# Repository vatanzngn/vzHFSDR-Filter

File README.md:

# Six Band 5th-Order Chebyshev Bandpass Filter Board for vzHFSDR HF/VHF

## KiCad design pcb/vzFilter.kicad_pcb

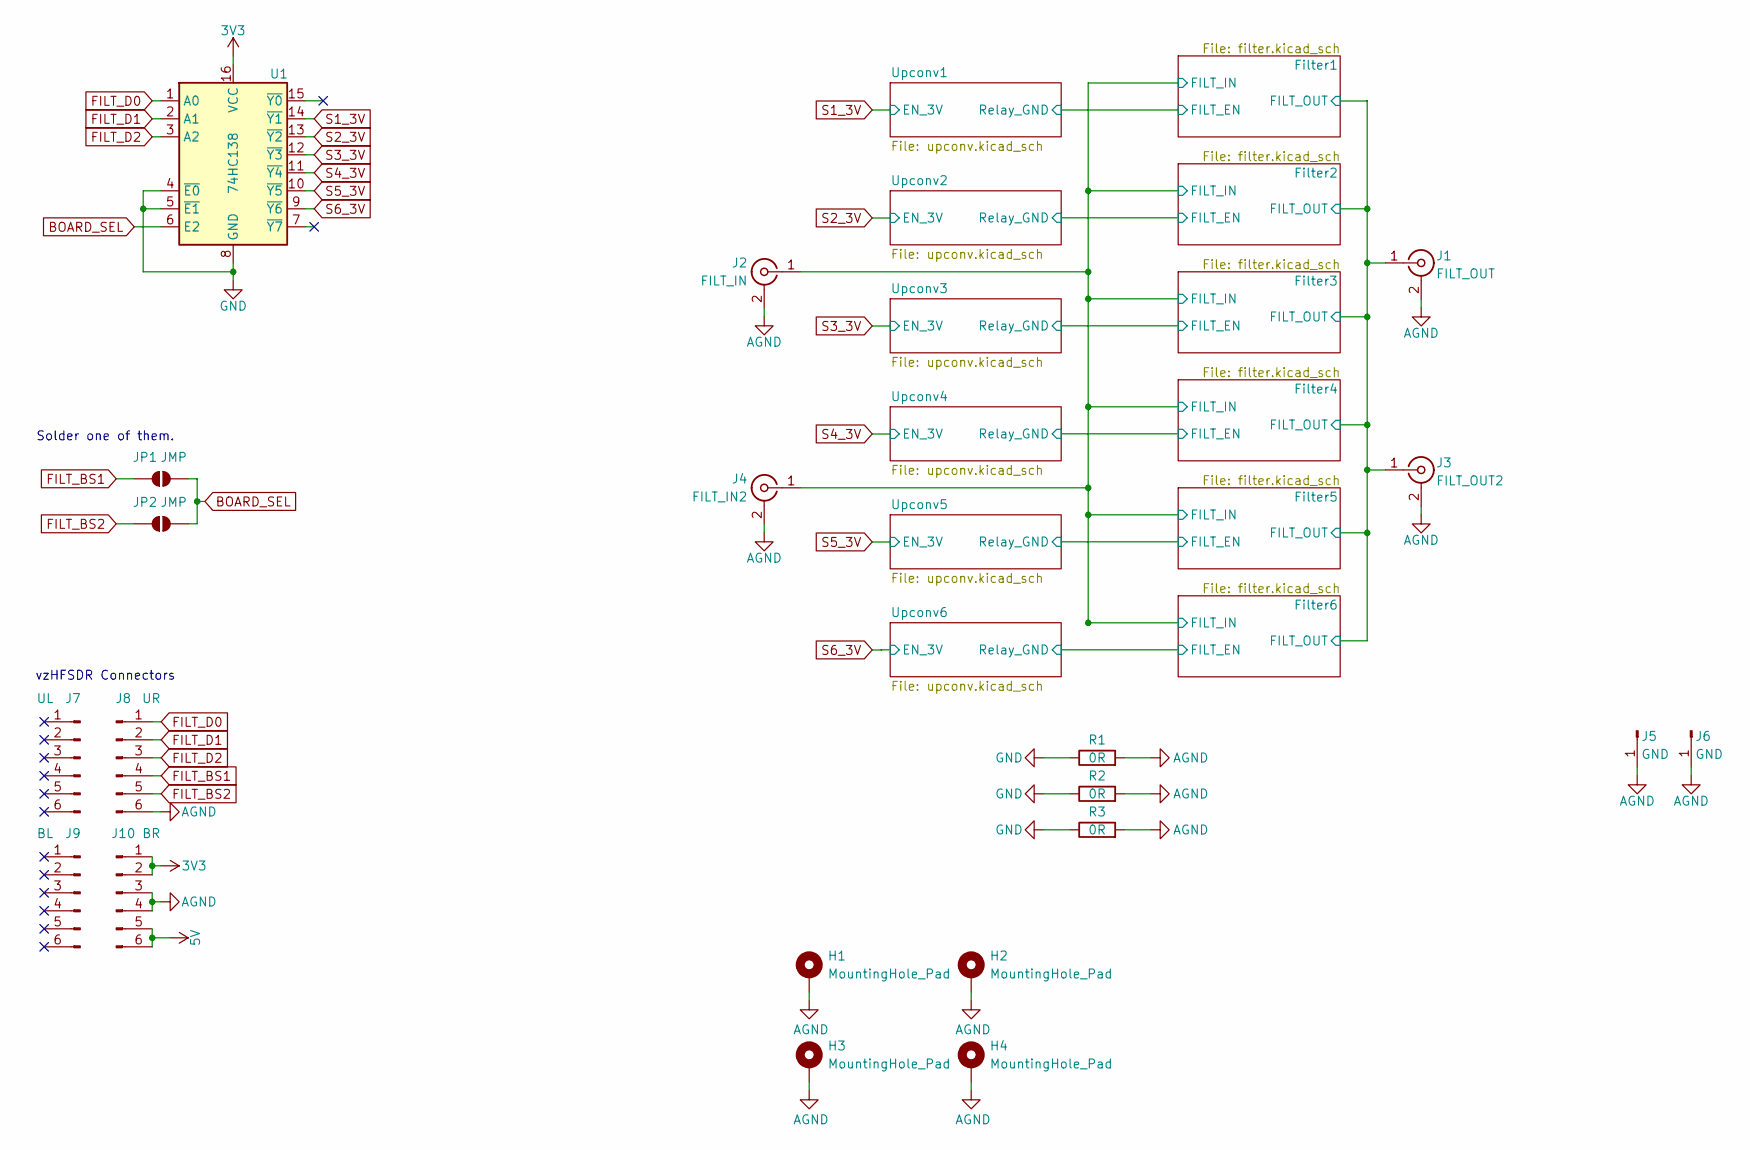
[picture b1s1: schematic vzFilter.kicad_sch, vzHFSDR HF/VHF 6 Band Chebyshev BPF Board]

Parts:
H1, H2, H3, H4: MountingHole_Pad; MountingHole_3.2mm_M3_Pad_Via
J1: FILT_OUT; SMA_BAT_Wireless_BWSMA-KWE-Z001
J2: FILT_IN; SMA_BAT_Wireless_BWSMA-KWE-Z001
J3: FILT_OUT2; SMA_BAT_Wireless_BWSMA-KWE-Z001
J4: FILT_IN2; SMA_BAT_Wireless_BWSMA-KWE-Z001
J5, J6: GND; GroundPad
J7: UL; PinSocket_1x06_P2.54mm_Vertical
J8: UR; PinSocket_1x06_P2.54mm_Vertical
J9: BL; PinSocket_1x06_P2.54mm_Vertical
J10: BR; PinSocket_1x06_P2.54mm_Vertical
JP1, JP2: JMP; SolderJumper-2_P1.3mm_Open_RoundedPad1.0x1.5mm
R1, R2, R3: 0R; R_0805_2012Metric_Pad1.20x1.40mm_HandSolder
U1: 74HC138; SOIC-16_3.9x9.9mm_P1.27mm

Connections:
3V3: J10.1, J10.2, U1.16 (VCC)
5V: J10.5, J10.6; also elsewhere on the board
/Filter1/FILT_IN: J2.1 (In), J4.1 (In); also elsewhere on the board
/Filter1/FILT_OUT: J1.1 (In), J3.1 (In); also elsewhere on the board
AGND: H1.1, H2.1, H3.1, H4.1, J1.2 (Ext), J2.2 (Ext), J3.2 (Ext), J4.2 (Ext), J5.1, J6.1, J8.6, J10.3, J10.4, R1.2, R2.2, R3.2; also elsewhere on the board
BOARD_SEL: JP1.2 (B), JP2.2 (B), U1.6 (E2)
FILT_BS1: J8.4, JP1.1 (A)
FILT_BS2: J8.5, JP2.1 (A)
FILT_D0: J8.1, U1.1 (A0)
FILT_D1: J8.2, U1.2 (A1)
FILT_D2: J8.3, U1.3 (A2)
GND: R1.1, R2.1, R3.1, U1.4 (~E0), U1.5 (~E1), U1.8 (GND); also elsewhere on the board
S1_3V: U1.14 (~Y1); also elsewhere on the board
S2_3V: U1.13 (~Y2); also elsewhere on the board
S3_3V: U1.12 (~Y3); also elsewhere on the board
S4_3V: U1.11 (~Y4); also elsewhere on the board
S5_3V: U1.10 (~Y5); also elsewhere on the board
S6_3V: U1.9 (~Y6); also elsewhere on the board

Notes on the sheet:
Solder one of them.
vzHFSDR Connectors

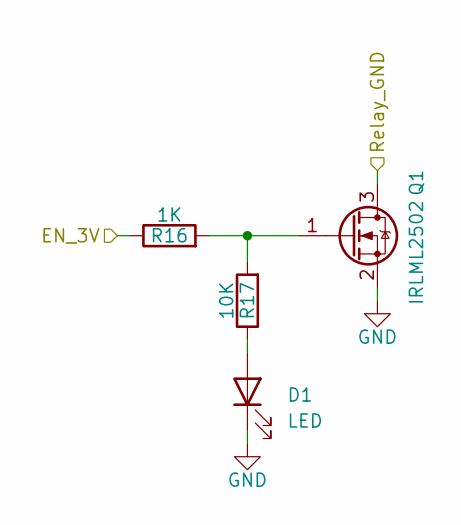
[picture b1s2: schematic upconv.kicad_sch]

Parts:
D1: LED; LED_0805_2012Metric_Pad1.15x1.40mm_HandSolder
Q1: IRLML2502; SOT-23
R16: 1K; R_0805_2012Metric_Pad1.20x1.40mm_HandSolder
R17: 10K; R_0805_2012Metric_Pad1.20x1.40mm_HandSolder

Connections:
/Filter1/FILT_EN: Q1.3 (D); also elsewhere on the board
GND: D1.1 (K), Q1.2 (S); also elsewhere on the board
unnamed: D1.2 (A), R17.1
unnamed: Q1.1 (G), R16.2, R17.2
S1_3V: R16.1; also elsewhere on the board

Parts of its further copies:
D2, D3, D4, D5, D6: LED; LED_0805_2012Metric_Pad1.15x1.40mm_HandSolder
Q2, Q3, Q4, Q5, Q6: IRLML2502; SOT-23
R18, R20, R22, R24, R26: 1K; R_0805_2012Metric_Pad1.20x1.40mm_HandSolder
R19, R21, R23, R25, R27: 10K; R_0805_2012Metric_Pad1.20x1.40mm_HandSolder

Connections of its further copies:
/Filter2/FILT_EN: Q2.3 (D); also elsewhere on the board
/Filter3/FILT_EN: Q3.3 (D); also elsewhere on the board
/Filter4/FILT_EN: Q4.3 (D); also elsewhere on the board
/Filter5/FILT_EN: Q5.3 (D); also elsewhere on the board
/Filter6/FILT_EN: Q6.3 (D); also elsewhere on the board
GND: D2.1 (K), D3.1 (K), D4.1 (K), D5.1 (K), D6.1 (K), Q2.2 (S), Q3.2 (S), Q4.2 (S), Q5.2 (S), Q6.2 (S); also elsewhere on the board
unnamed: D2.2 (A), R19.1
unnamed: D3.2 (A), R21.1
unnamed: D4.2 (A), R23.1
unnamed: D5.2 (A), R25.1
unnamed: D6.2 (A), R27.1
unnamed: Q2.1 (G), R18.2, R19.2
unnamed: Q3.1 (G), R20.2, R21.2
unnamed: Q4.1 (G), R22.2, R23.2
unnamed: Q5.1 (G), R24.2, R25.2
unnamed: Q6.1 (G), R26.2, R27.2
S2_3V: R18.1; also elsewhere on the board
S3_3V: R20.1; also elsewhere on the board
S4_3V: R22.1; also elsewhere on the board
S5_3V: R24.1; also elsewhere on the board
S6_3V: R26.1; also elsewhere on the board

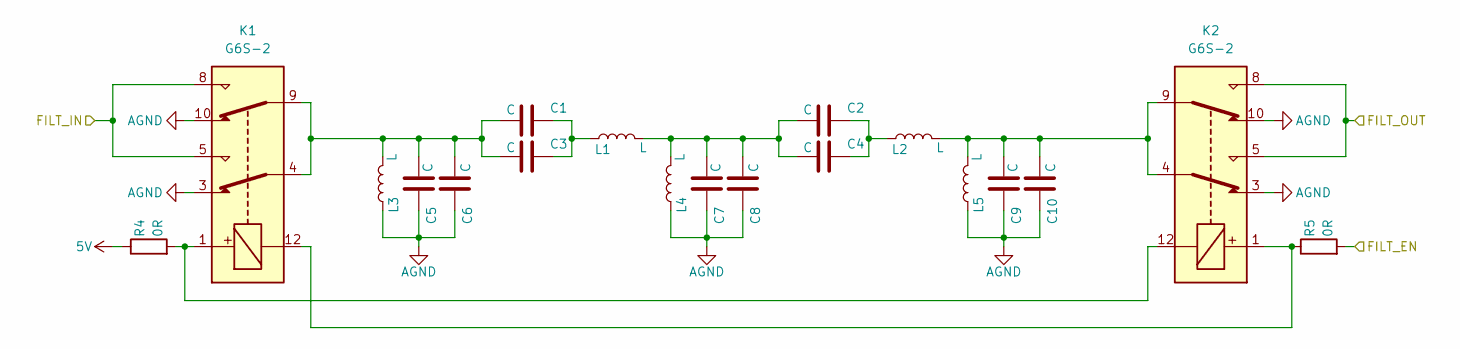
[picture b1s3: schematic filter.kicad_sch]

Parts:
C1, C2, C3, C4, C5, C6, C7, C8, C9, C10: C; C_0805_2012Metric_Pad1.18x1.45mm_HandSolder
K1, K2: G6S-2; Relay_DPDT_Omron_G6S-2
L1, L2, L3, L4, L5: L; T68-2 Toroid
R4, R5: 0R; R_1206_3216Metric

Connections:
5V: R4.1; also elsewhere on the board
/Filter1/FILT_EN: R5.2; also elsewhere on the board
/Filter1/FILT_IN: K1.5, K1.8; also elsewhere on the board
/Filter1/FILT_OUT: K2.5, K2.8; also elsewhere on the board
AGND: C5.2, C6.2, C7.2, C8.2, C9.2, C10.2, K1.3, K1.10, K2.3, K2.10, L3.1, L4.1, L5.1; also elsewhere on the board
unnamed: C1.1, C3.1, C5.1, C6.1, K1.4, K1.9, L3.2
unnamed: C1.2, C3.2, L1.1
unnamed: C2.1, C4.1, C7.1, C8.1, L1.2, L4.2
unnamed: C2.2, C4.2, L2.1
unnamed: C9.1, C10.1, K2.4, K2.9, L2.2, L5.2
unnamed: K1.1, K2.12, R4.2
unnamed: K1.12, K2.1, R5.1

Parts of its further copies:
C11, C12, C13, C14, C15, C16, C17, C18, C19, C20, C21, C22, C23, C24, C25, C26, C27, C28, C29, C30, C31, C32, C33, C34, C35, C36, C37, C38, C39, C40, C41, C42, C43, C44, C45, C46, C47, C48, C49, C50, C51, C52, C53, C54, C55, C56, C57, C58, C59, C60: C; C_0805_2012Metric_Pad1.18x1.45mm_HandSolder
K3, K4, K5, K6, K7, K8, K9, K10, K11, K12: G6S-2; Relay_DPDT_Omron_G6S-2
L6, L7, L8, L9, L10, L11, L12, L13, L14, L15, L16, L17, L18, L19, L20, L21, L22, L23, L24, L25, L26, L27, L28, L29, L30: L; T68-2 Toroid
R6, R7, R8, R9, R10, R11, R12, R13, R14, R15: 0R; R_1206_3216Metric

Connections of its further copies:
5V: R6.1, R8.1, R10.1, R12.1, R14.1; also elsewhere on the board
/Filter1/FILT_IN: K3.5, K3.8, K5.5, K5.8, K7.5, K7.8, K9.5, K9.8, K11.5, K11.8; also elsewhere on the board
/Filter1/FILT_OUT: K4.5, K4.8, K6.5, K6.8, K8.5, K8.8, K10.5, K10.8, K12.5, K12.8; also elsewhere on the board
/Filter2/FILT_EN: R7.2; also elsewhere on the board
/Filter3/FILT_EN: R9.2; also elsewhere on the board
/Filter4/FILT_EN: R11.2; also elsewhere on the board
/Filter5/FILT_EN: R13.2; also elsewhere on the board
/Filter6/FILT_EN: R15.2; also elsewhere on the board
AGND: C15.2, C16.2, C17.2, C18.2, C19.2, C20.2, C25.2, C26.2, C27.2, C28.2, C29.2, C30.2, C35.2, C36.2, C37.2, C38.2, C39.2, C40.2, C45.2, C46.2, C47.2, C48.2, C49.2, C50.2, C55.2, C56.2, C57.2, C58.2, C59.2, C60.2, K3.3, K3.10, K4.3, K4.10, K5.3, K5.10, K6.3, K6.10, K7.3, K7.10, K8.3, K8.10, K9.3, K9.10, K10.3, K10.10, K11.3, K11.10, K12.3, K12.10, L8.1, L9.1, L10.1, L13.1, L14.1, L15.1, L18.1, L19.1, L20.1, L23.1, L24.1, L25.1, L28.1, L29.1, L30.1; also elsewhere on the board
unnamed: C11.1, C13.1, C15.1, C16.1, K3.4, K3.9, L8.2
unnamed: C11.2, C13.2, L6.1
unnamed: C12.1, C14.1, C17.1, C18.1, L6.2, L9.2
unnamed: C12.2, C14.2, L7.1
unnamed: C19.1, C20.1, K4.4, K4.9, L7.2, L10.2
unnamed: C21.1, C23.1, C25.1, C26.1, K5.4, K5.9, L13.2
unnamed: C21.2, C23.2, L11.1
unnamed: C22.1, C24.1, C27.1, C28.1, L11.2, L14.2
unnamed: C22.2, C24.2, L12.1
unnamed: C29.1, C30.1, K6.4, K6.9, L12.2, L15.2
unnamed: C31.1, C33.1, C35.1, C36.1, K7.4, K7.9, L18.2
unnamed: C31.2, C33.2, L16.1
unnamed: C32.1, C34.1, C37.1, C38.1, L16.2, L19.2
unnamed: C32.2, C34.2, L17.1
unnamed: C39.1, C40.1, K8.4, K8.9, L17.2, L20.2
unnamed: C41.1, C43.1, C45.1, C46.1, K9.4, K9.9, L23.2
unnamed: C41.2, C43.2, L21.1
unnamed: C42.1, C44.1, C47.1, C48.1, L21.2, L24.2
unnamed: C42.2, C44.2, L22.1
unnamed: C49.1, C50.1, K10.4, K10.9, L22.2, L25.2
unnamed: C51.1, C53.1, C55.1, C56.1, K11.4, K11.9, L28.2
unnamed: C51.2, C53.2, L26.1
unnamed: C52.1, C54.1, C57.1, C58.1, L26.2, L29.2
unnamed: C52.2, C54.2, L27.1
unnamed: C59.1, C60.1, K12.4, K12.9, L27.2, L30.2
unnamed: K3.1, K4.12, R6.2
unnamed: K3.12, K4.1, R7.1
unnamed: K5.1, K6.12, R8.2
unnamed: K5.12, K6.1, R9.1
unnamed: K7.1, K8.12, R10.2
unnamed: K7.12, K8.1, R11.1
unnamed: K9.12, K10.1, R13.1
unnamed: K9.1, K10.12, R12.2
unnamed: K11.1, K12.12, R14.2
unnamed: K11.12, K12.1, R15.1

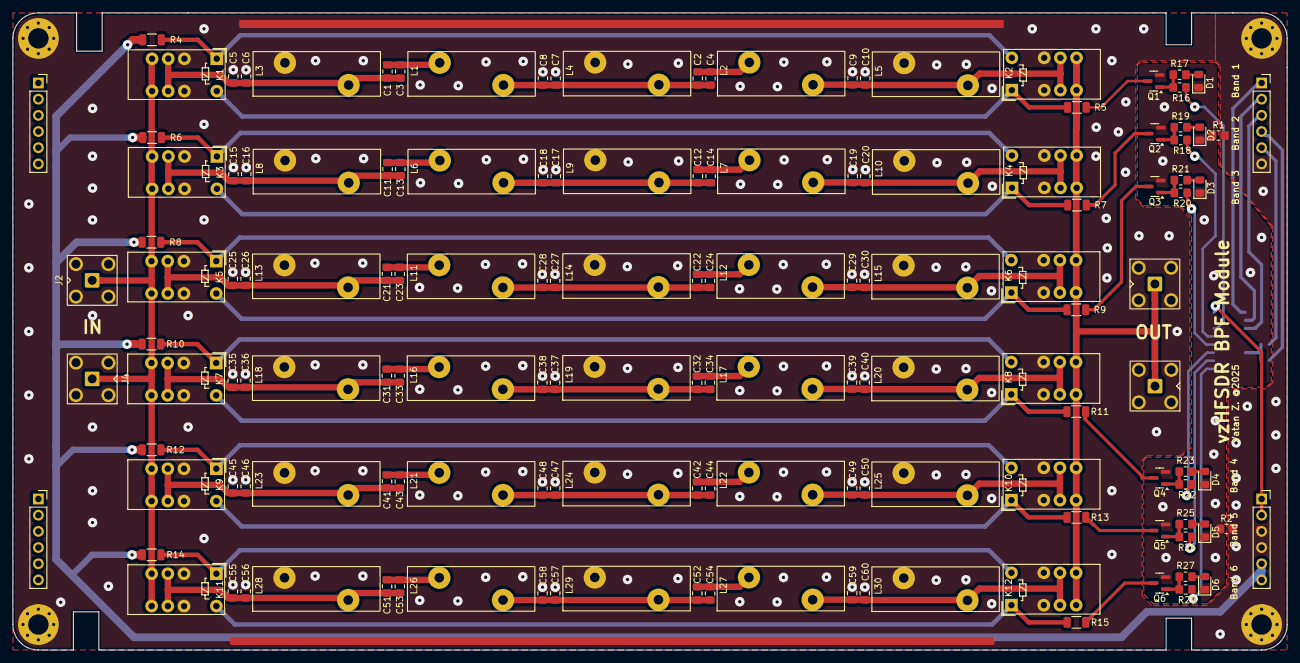
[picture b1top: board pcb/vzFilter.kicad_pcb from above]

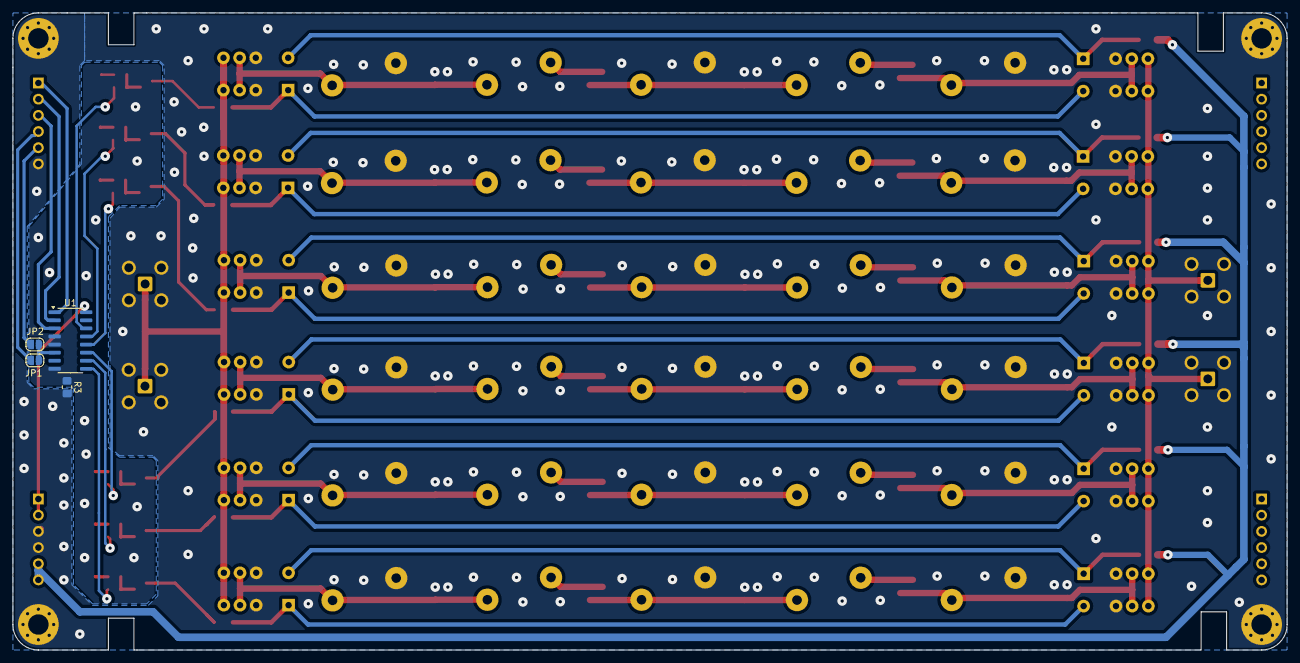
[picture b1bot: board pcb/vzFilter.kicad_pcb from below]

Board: 2 copper layers, 200.0 x 100.0 mm, 158 parts (4 on the bottom side), 78 nets.

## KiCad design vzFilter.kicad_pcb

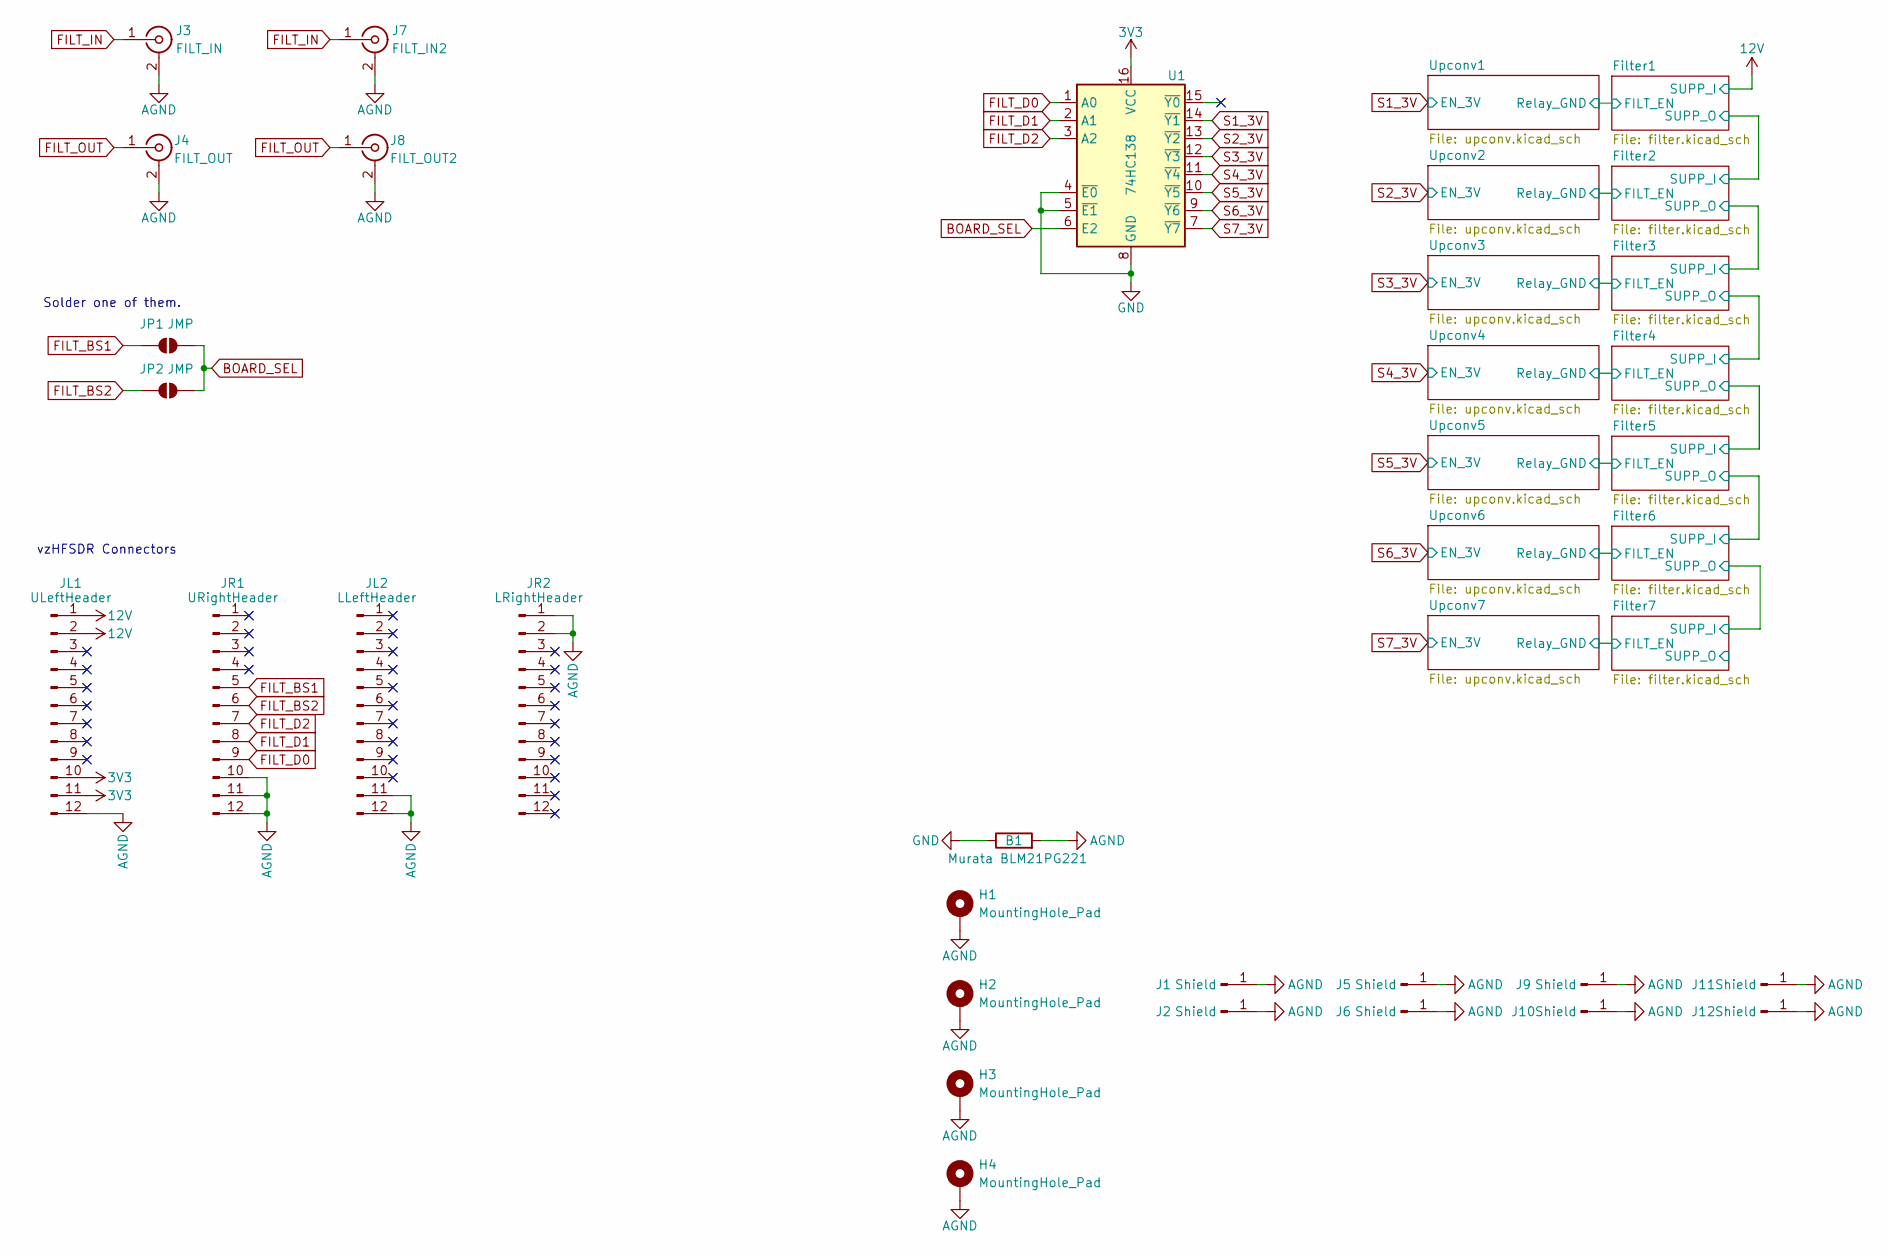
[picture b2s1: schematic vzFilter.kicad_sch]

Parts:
B1: Murata BLM21PG221; R_0805_2012Metric
H1, H2, H3, H4: MountingHole_Pad; MountingHole_3.2mm_M3_ISO14580_Pad_TopBottom
J1, J2, J5, J6, J9, J10, J11, J12: Shield; Untitled_2
J3: FILT_IN; U.FL_Molex_MCRF_73412-0110_Vertical
J4: FILT_OUT; U.FL_Molex_MCRF_73412-0110_Vertical
J7: FILT_IN2; U.FL_Molex_MCRF_73412-0110_Vertical
J8: FILT_OUT2; U.FL_Molex_MCRF_73412-0110_Vertical
JL1: ULeftHeader; PinSocket_1x12_P2.54mm_Vertical
JL2: LLeftHeader; PinSocket_1x12_P2.54mm_Vertical
JP1, JP2: JMP; SolderJumper-2_P1.3mm_Open_RoundedPad1.0x1.5mm
JR1: URightHeader; PinSocket_1x12_P2.54mm_Vertical
JR2: LRightHeader; PinSocket_1x12_P2.54mm_Vertical
U1: 74HC138; SOIC-16_3.9x9.9mm_P1.27mm

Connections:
3V3: JL1.10, JL1.11, U1.16 (VCC)
12V: JL1.1, JL1.2; also elsewhere on the board
AGND: B1.2, H1.1, H2.1, H3.1, H4.1, J1.1, J2.1, J3.2 (Ext), J4.2 (Ext), J5.1, J6.1, J7.2 (Ext), J8.2 (Ext), J9.1, J10.1, J11.1, J12.1, JL1.12, JL2.11, JL2.12, JR1.10, JR1.11, JR1.12, JR2.1, JR2.2; also elsewhere on the board
BOARD_SEL: JP1.2 (B), JP2.2 (B), U1.6 (E2)
FILT_BS1: JP1.1 (A), JR1.5
FILT_BS2: JP2.1 (A), JR1.6
FILT_D0: JR1.9, U1.1 (A0)
FILT_D1: JR1.8, U1.2 (A1)
FILT_D2: JR1.7, U1.3 (A2)
FILT_IN: J3.1 (In), J7.1 (In); also elsewhere on the board
FILT_OUT: J4.1 (In), J8.1 (In); also elsewhere on the board
GND: B1.1, U1.4 (~E0), U1.5 (~E1), U1.8 (GND); also elsewhere on the board
S1_3V: U1.14 (~Y1); also elsewhere on the board
S2_3V: U1.13 (~Y2); also elsewhere on the board
S3_3V: U1.12 (~Y3); also elsewhere on the board
S4_3V: U1.11 (~Y4); also elsewhere on the board
S5_3V: U1.10 (~Y5); also elsewhere on the board
S6_3V: U1.9 (~Y6); also elsewhere on the board
S7_3V: U1.7 (~Y7); also elsewhere on the board

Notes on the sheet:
Solder one of them.
vzHFSDR Connectors

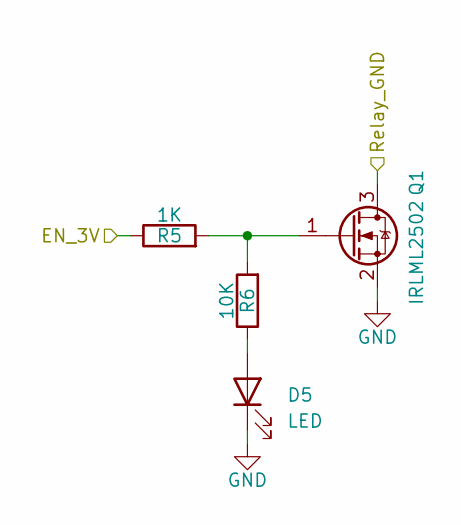
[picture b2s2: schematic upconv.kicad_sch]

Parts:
D5: LED; LED_0805_2012Metric_Pad1.15x1.40mm_HandSolder
Q1: IRLML2502; SOT-23
R5: 1K; R_0805_2012Metric_Pad1.20x1.40mm_HandSolder
R6: 10K; R_0805_2012Metric_Pad1.20x1.40mm_HandSolder

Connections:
/Filter2/FILT_EN: Q1.3 (D); also elsewhere on the board
GND: D5.1 (K), Q1.2 (S); also elsewhere on the board
unnamed: D5.2 (A), R6.1
unnamed: Q1.1 (G), R5.2, R6.2
S2_3V: R5.1; also elsewhere on the board

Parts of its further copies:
D8, D11, D12, D15, D18, D21: LED; LED_0805_2012Metric_Pad1.15x1.40mm_HandSolder
Q2, Q3, Q4, Q5, Q6, Q7: IRLML2502; SOT-23
R9, R13, R15, R19, R23, R27: 1K; R_0805_2012Metric_Pad1.20x1.40mm_HandSolder
R10, R14, R16, R20, R24, R28: 10K; R_0805_2012Metric_Pad1.20x1.40mm_HandSolder

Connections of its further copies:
/Filter1/FILT_EN: Q3.3 (D); also elsewhere on the board
/Filter3/FILT_EN: Q2.3 (D); also elsewhere on the board
/Filter4/FILT_EN: Q4.3 (D); also elsewhere on the board
/Filter5/FILT_EN: Q5.3 (D); also elsewhere on the board
/Filter6/FILT_EN: Q6.3 (D); also elsewhere on the board
/Filter7/FILT_EN: Q7.3 (D); also elsewhere on the board
GND: D8.1 (K), D11.1 (K), D12.1 (K), D15.1 (K), D18.1 (K), D21.1 (K), Q2.2 (S), Q3.2 (S), Q4.2 (S), Q5.2 (S), Q6.2 (S), Q7.2 (S); also elsewhere on the board
unnamed: D8.2 (A), R10.1
unnamed: D11.2 (A), R14.1
unnamed: D12.2 (A), R16.1
unnamed: D15.2 (A), R20.1
unnamed: D18.2 (A), R24.1
unnamed: D21.2 (A), R28.1
unnamed: Q2.1 (G), R9.2, R10.2
unnamed: Q3.1 (G), R13.2, R14.2
unnamed: Q4.1 (G), R15.2, R16.2
unnamed: Q5.1 (G), R19.2, R20.2
unnamed: Q6.1 (G), R23.2, R24.2
unnamed: Q7.1 (G), R27.2, R28.2
S1_3V: R13.1; also elsewhere on the board
S3_3V: R9.1; also elsewhere on the board
S4_3V: R15.1; also elsewhere on the board
S5_3V: R19.1; also elsewhere on the board
S6_3V: R23.1; also elsewhere on the board
S7_3V: R27.1; also elsewhere on the board

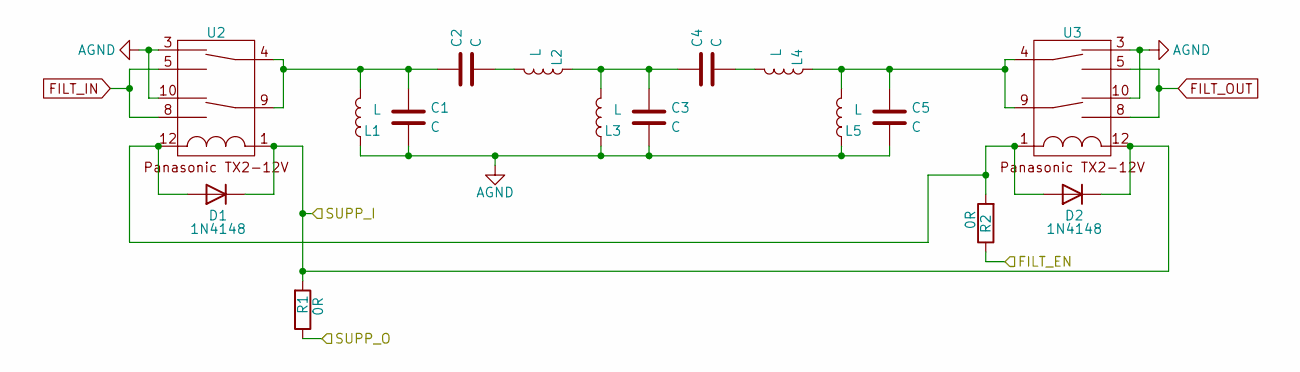
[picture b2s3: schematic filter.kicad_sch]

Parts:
C1, C2, C3, C4, C5: C; C_0805_2012Metric_Pad1.18x1.45mm_HandSolder
D1, D2: 1N4148; D_DO-35_SOD27_P7.62mm_Horizontal
L1, L2, L3, L4, L5: L; vz_torroite_t68
R1, R2: 0R; R_1210_3225Metric_Pad1.30x2.65mm_HandSolder
U2, U3: TX2_Panasonic

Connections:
12V: D1.1 (K), D2.1 (K), R1.2, U2.1, U3.12; also elsewhere on the board
/Filter1/FILT_EN: R2.1; also elsewhere on the board
/Filter1/SUPP_O: R1.1; also elsewhere on the board
AGND: C1.2, C3.2, C5.2, L1.1, L3.1, L5.1, U2.3, U2.10, U3.3, U3.10; also elsewhere on the board
FILT_IN: U2.5, U2.8; also elsewhere on the board
FILT_OUT: U3.5, U3.8; also elsewhere on the board
unnamed: C1.1, C2.1, L1.2, U2.4, U2.9
unnamed: C2.2, L2.2
unnamed: C3.1, C4.1, L2.1, L3.2
unnamed: C4.2, L4.2
unnamed: C5.1, L4.1, L5.2, U3.4, U3.9
unnamed: D1.2 (A), D2.2 (A), R2.2, U2.12, U3.1

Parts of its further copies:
C6, C7, C8, C9, C10, C11, C12, C13, C14, C15, C16, C17, C18, C19, C20, C21, C22, C23, C24, C25, C26, C27, C28, C29, C30, C31, C32, C33, C34, C35: C; C_0805_2012Metric_Pad1.18x1.45mm_HandSolder
D3, D4, D6, D7, D9, D10, D13, D14, D16, D17, D19, D20: 1N4148; D_DO-35_SOD27_P7.62mm_Horizontal
L6, L7, L8, L9, L10, L11, L12, L13, L14, L15, L16, L17, L18, L19, L20, L21, L22, L23, L24, L25, L26, L27, L28, L29, L30, L31, L32, L33, L34, L35: L; vz_torroite_t68
R3, R4, R7, R8, R11, R12, R17, R18, R21, R22, R25, R26: 0R; R_1210_3225Metric_Pad1.30x2.65mm_HandSolder
U4, U5, U6, U7, U8, U9, U10, U11, U12, U13, U14, U15: TX2_Panasonic

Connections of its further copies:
/Filter1/SUPP_O: D3.1 (K), D4.1 (K), R3.2, U4.1, U5.12; also elsewhere on the board
/Filter2/FILT_EN: R4.1; also elsewhere on the board
/Filter2/SUPP_O: D6.1 (K), D7.1 (K), R3.1, R7.2, U6.1, U7.12
/Filter3/FILT_EN: R8.1; also elsewhere on the board
/Filter3/SUPP_O: D9.1 (K), D10.1 (K), R7.1, R11.2, U8.1, U9.12
/Filter4/FILT_EN: R12.1; also elsewhere on the board
/Filter4/SUPP_O: D13.1 (K), D14.1 (K), R11.1, R17.2, U10.1, U11.12
/Filter5/FILT_EN: R18.1; also elsewhere on the board
/Filter5/SUPP_O: D16.1 (K), D17.1 (K), R17.1, R21.2, U12.1, U13.12
/Filter6/FILT_EN: R22.1; also elsewhere on the board
/Filter6/SUPP_O: D19.1 (K), D20.1 (K), R21.1, R25.2, U14.1, U15.12
/Filter7/FILT_EN: R26.1; also elsewhere on the board
/Filter7/SUPP_O: R25.1
AGND: C6.2, C8.2, C10.2, C11.2, C13.2, C15.2, C16.2, C18.2, C20.2, C21.2, C23.2, C25.2, C26.2, C28.2, C30.2, C31.2, C33.2, C35.2, L6.1, L8.1, L10.1, L11.1, L13.1, L15.1, L16.1, L18.1, L20.1, L21.1, L23.1, L25.1, L26.1, L28.1, L30.1, L31.1, L33.1, L35.1, U4.3, U4.10, U5.3, U5.10, U6.3, U6.10, U7.3, U7.10, U8.3, U8.10, U9.3, U9.10, U10.3, U10.10, U11.3, U11.10, U12.3, U12.10, U13.3, U13.10, U14.3, U14.10, U15.3, U15.10; also elsewhere on the board
FILT_IN: U4.5, U4.8, U6.5, U6.8, U8.5, U8.8, U10.5, U10.8, U12.5, U12.8, U14.5, U14.8; also elsewhere on the board
FILT_OUT: U5.5, U5.8, U7.5, U7.8, U9.5, U9.8, U11.5, U11.8, U13.5, U13.8, U15.5, U15.8; also elsewhere on the board
unnamed: C6.1, C7.1, L6.2, U4.4, U4.9
unnamed: C7.2, L7.2
unnamed: C8.1, C9.1, L7.1, L8.2
unnamed: C9.2, L9.2
unnamed: C10.1, L9.1, L10.2, U5.4, U5.9
unnamed: C11.1, C12.1, L11.2, U6.4, U6.9
unnamed: C12.2, L12.2
unnamed: C13.1, C14.1, L12.1, L13.2
unnamed: C14.2, L14.2
unnamed: C15.1, L14.1, L15.2, U7.4, U7.9
unnamed: C16.1, C17.1, L16.2, U8.4, U8.9
unnamed: C17.2, L17.2
unnamed: C18.1, C19.1, L17.1, L18.2
unnamed: C19.2, L19.2
unnamed: C20.1, L19.1, L20.2, U9.4, U9.9
unnamed: C21.1, C22.1, L21.2, U10.4, U10.9
unnamed: C22.2, L22.2
unnamed: C23.1, C24.1, L22.1, L23.2
unnamed: C24.2, L24.2
unnamed: C25.1, L24.1, L25.2, U11.4, U11.9
unnamed: C26.1, C27.1, L26.2, U12.4, U12.9
unnamed: C27.2, L27.2
unnamed: C28.1, C29.1, L27.1, L28.2
unnamed: C29.2, L29.2
unnamed: C30.1, L29.1, L30.2, U13.4, U13.9
unnamed: C31.1, C32.1, L31.2, U14.4, U14.9
unnamed: C32.2, L32.2
unnamed: C33.1, C34.1, L32.1, L33.2
unnamed: C34.2, L34.2
unnamed: C35.1, L34.1, L35.2, U15.4, U15.9
unnamed: D3.2 (A), D4.2 (A), R4.2, U4.12, U5.1
unnamed: D6.2 (A), D7.2 (A), R8.2, U6.12, U7.1
unnamed: D9.2 (A), D10.2 (A), R12.2, U8.12, U9.1
unnamed: D13.2 (A), D14.2 (A), R18.2, U10.12, U11.1
unnamed: D16.2 (A), D17.2 (A), R22.2, U12.12, U13.1
unnamed: D19.2 (A), D20.2 (A), R26.2, U14.12, U15.1

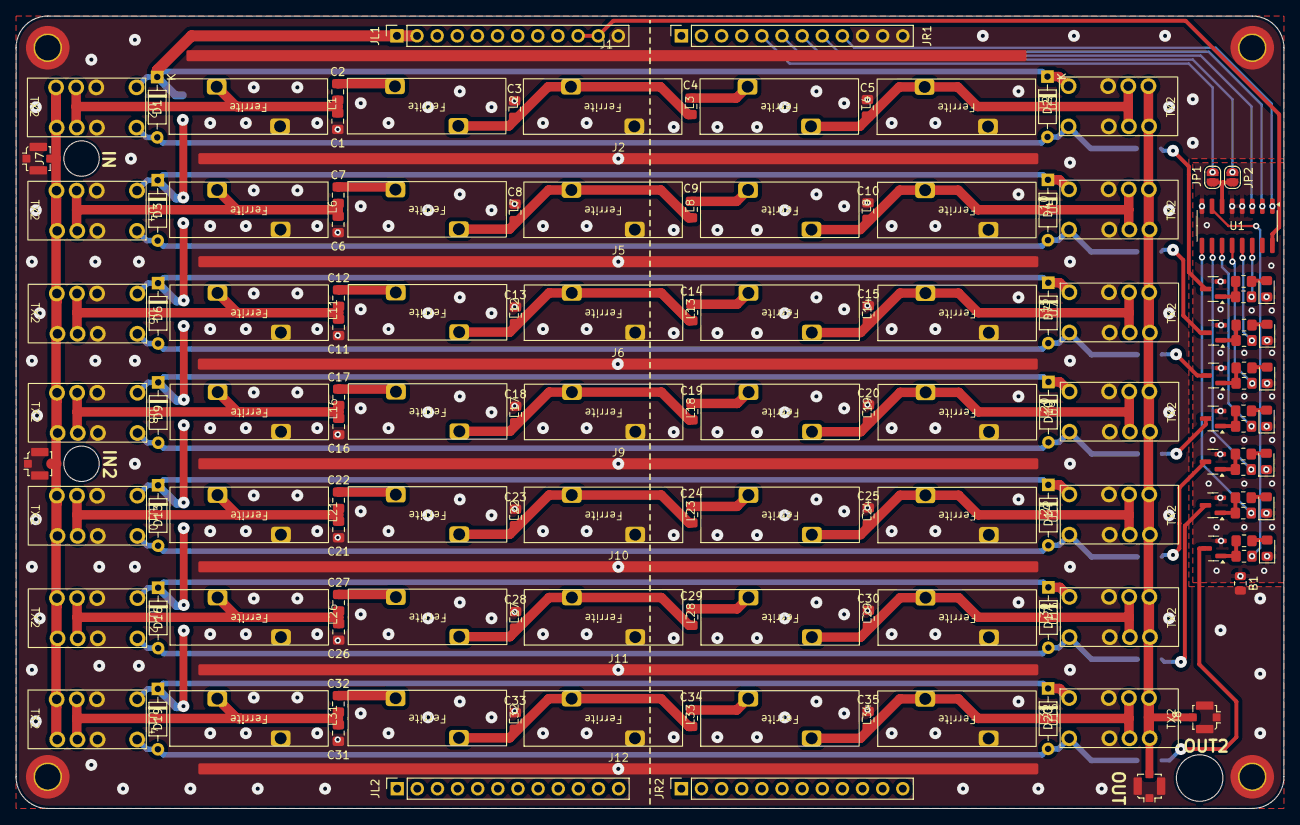
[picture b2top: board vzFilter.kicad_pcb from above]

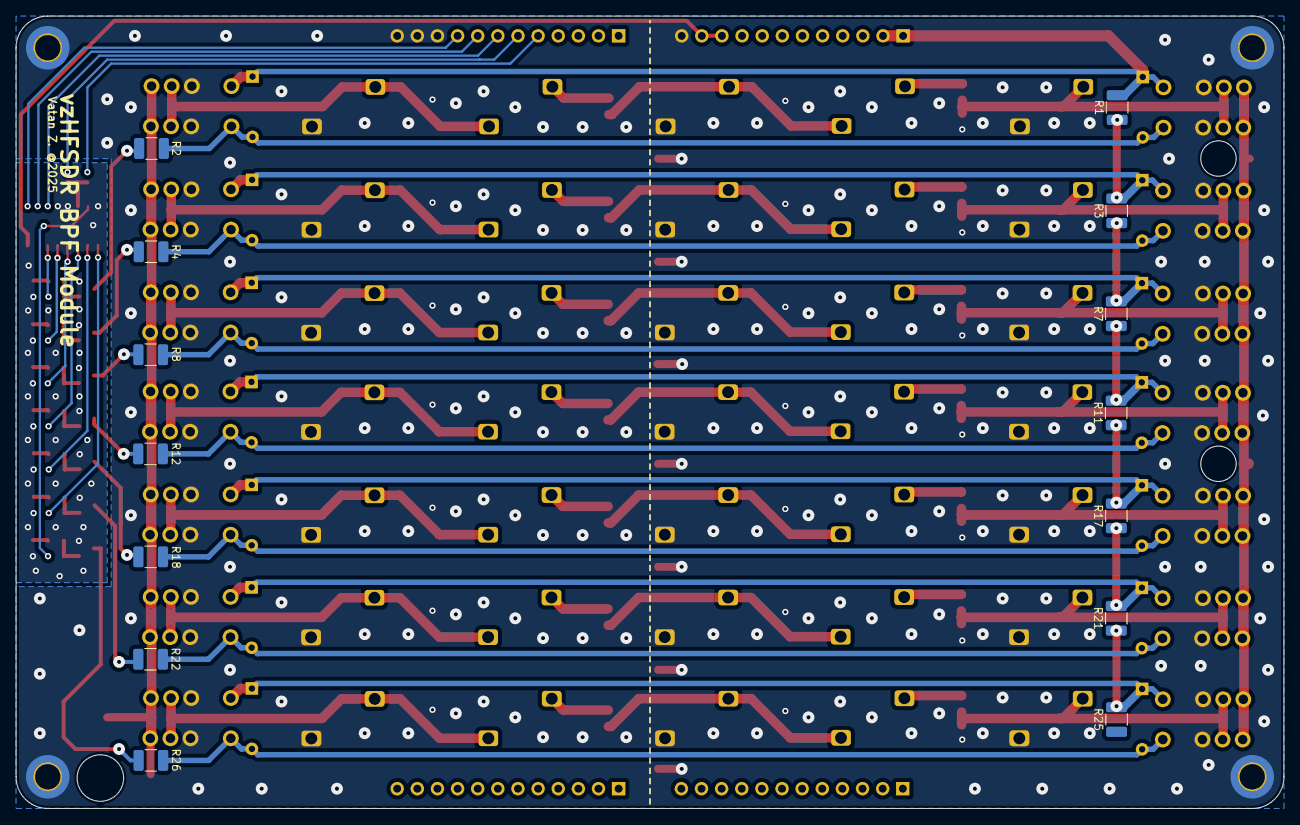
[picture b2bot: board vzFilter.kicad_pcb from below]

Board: 2 copper layers, 160.0 x 100.0 mm, 164 parts (14 on the bottom side), 88 nets.

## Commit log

2025-04-27 PCB upload
2025-08-08 New File Structure, OMRON G6S Upadate
2025-08-08 Gerber Generated.
